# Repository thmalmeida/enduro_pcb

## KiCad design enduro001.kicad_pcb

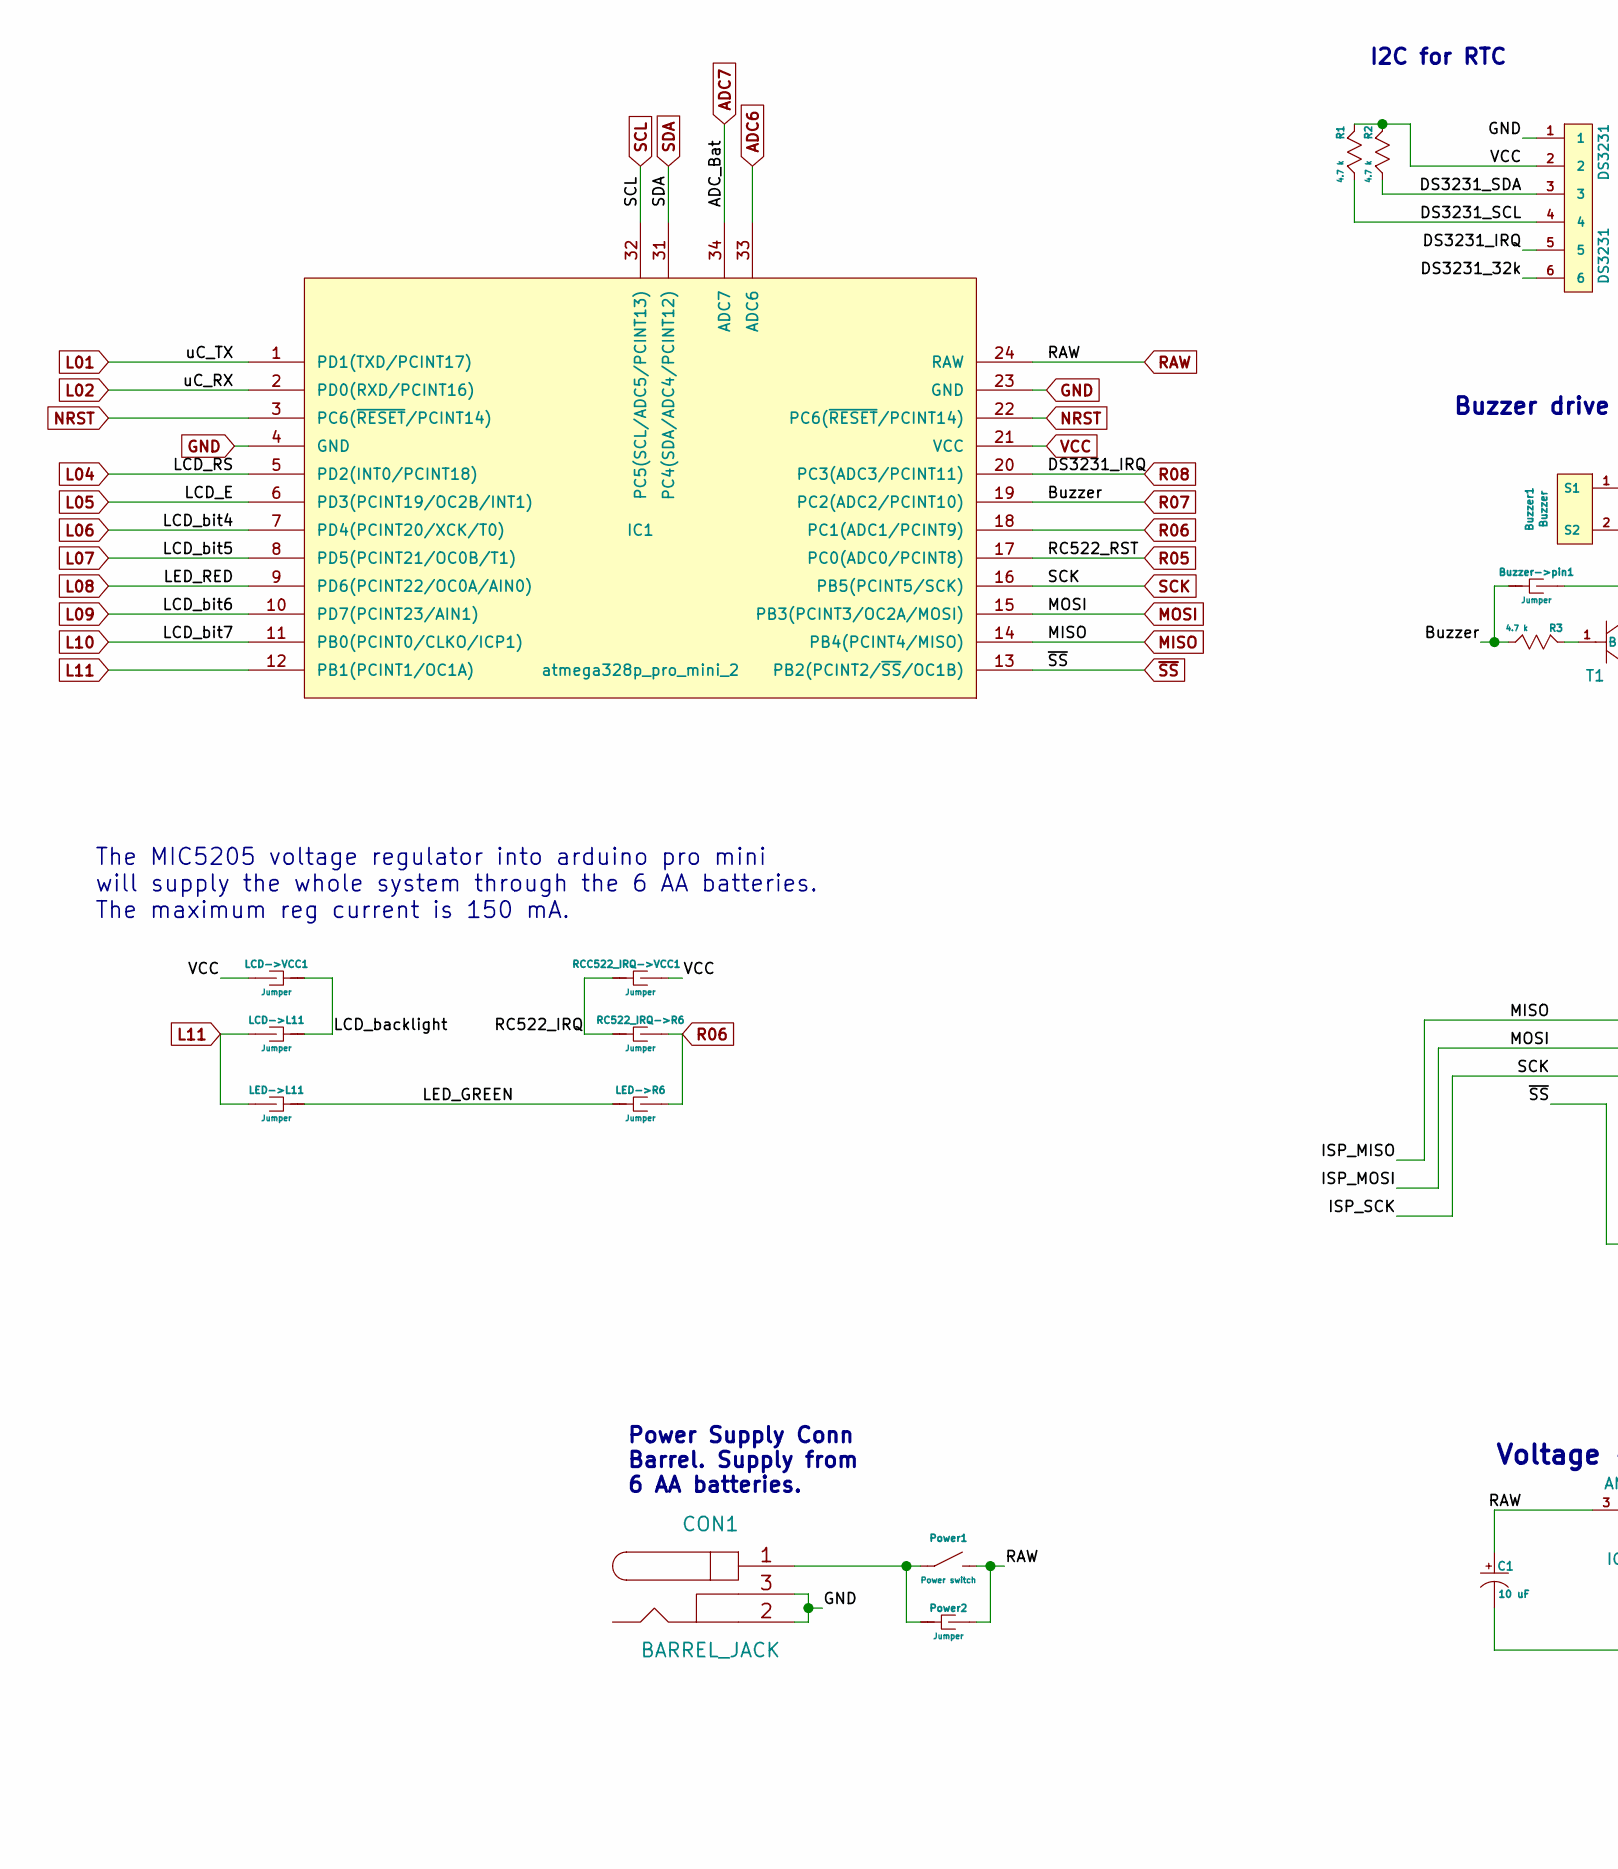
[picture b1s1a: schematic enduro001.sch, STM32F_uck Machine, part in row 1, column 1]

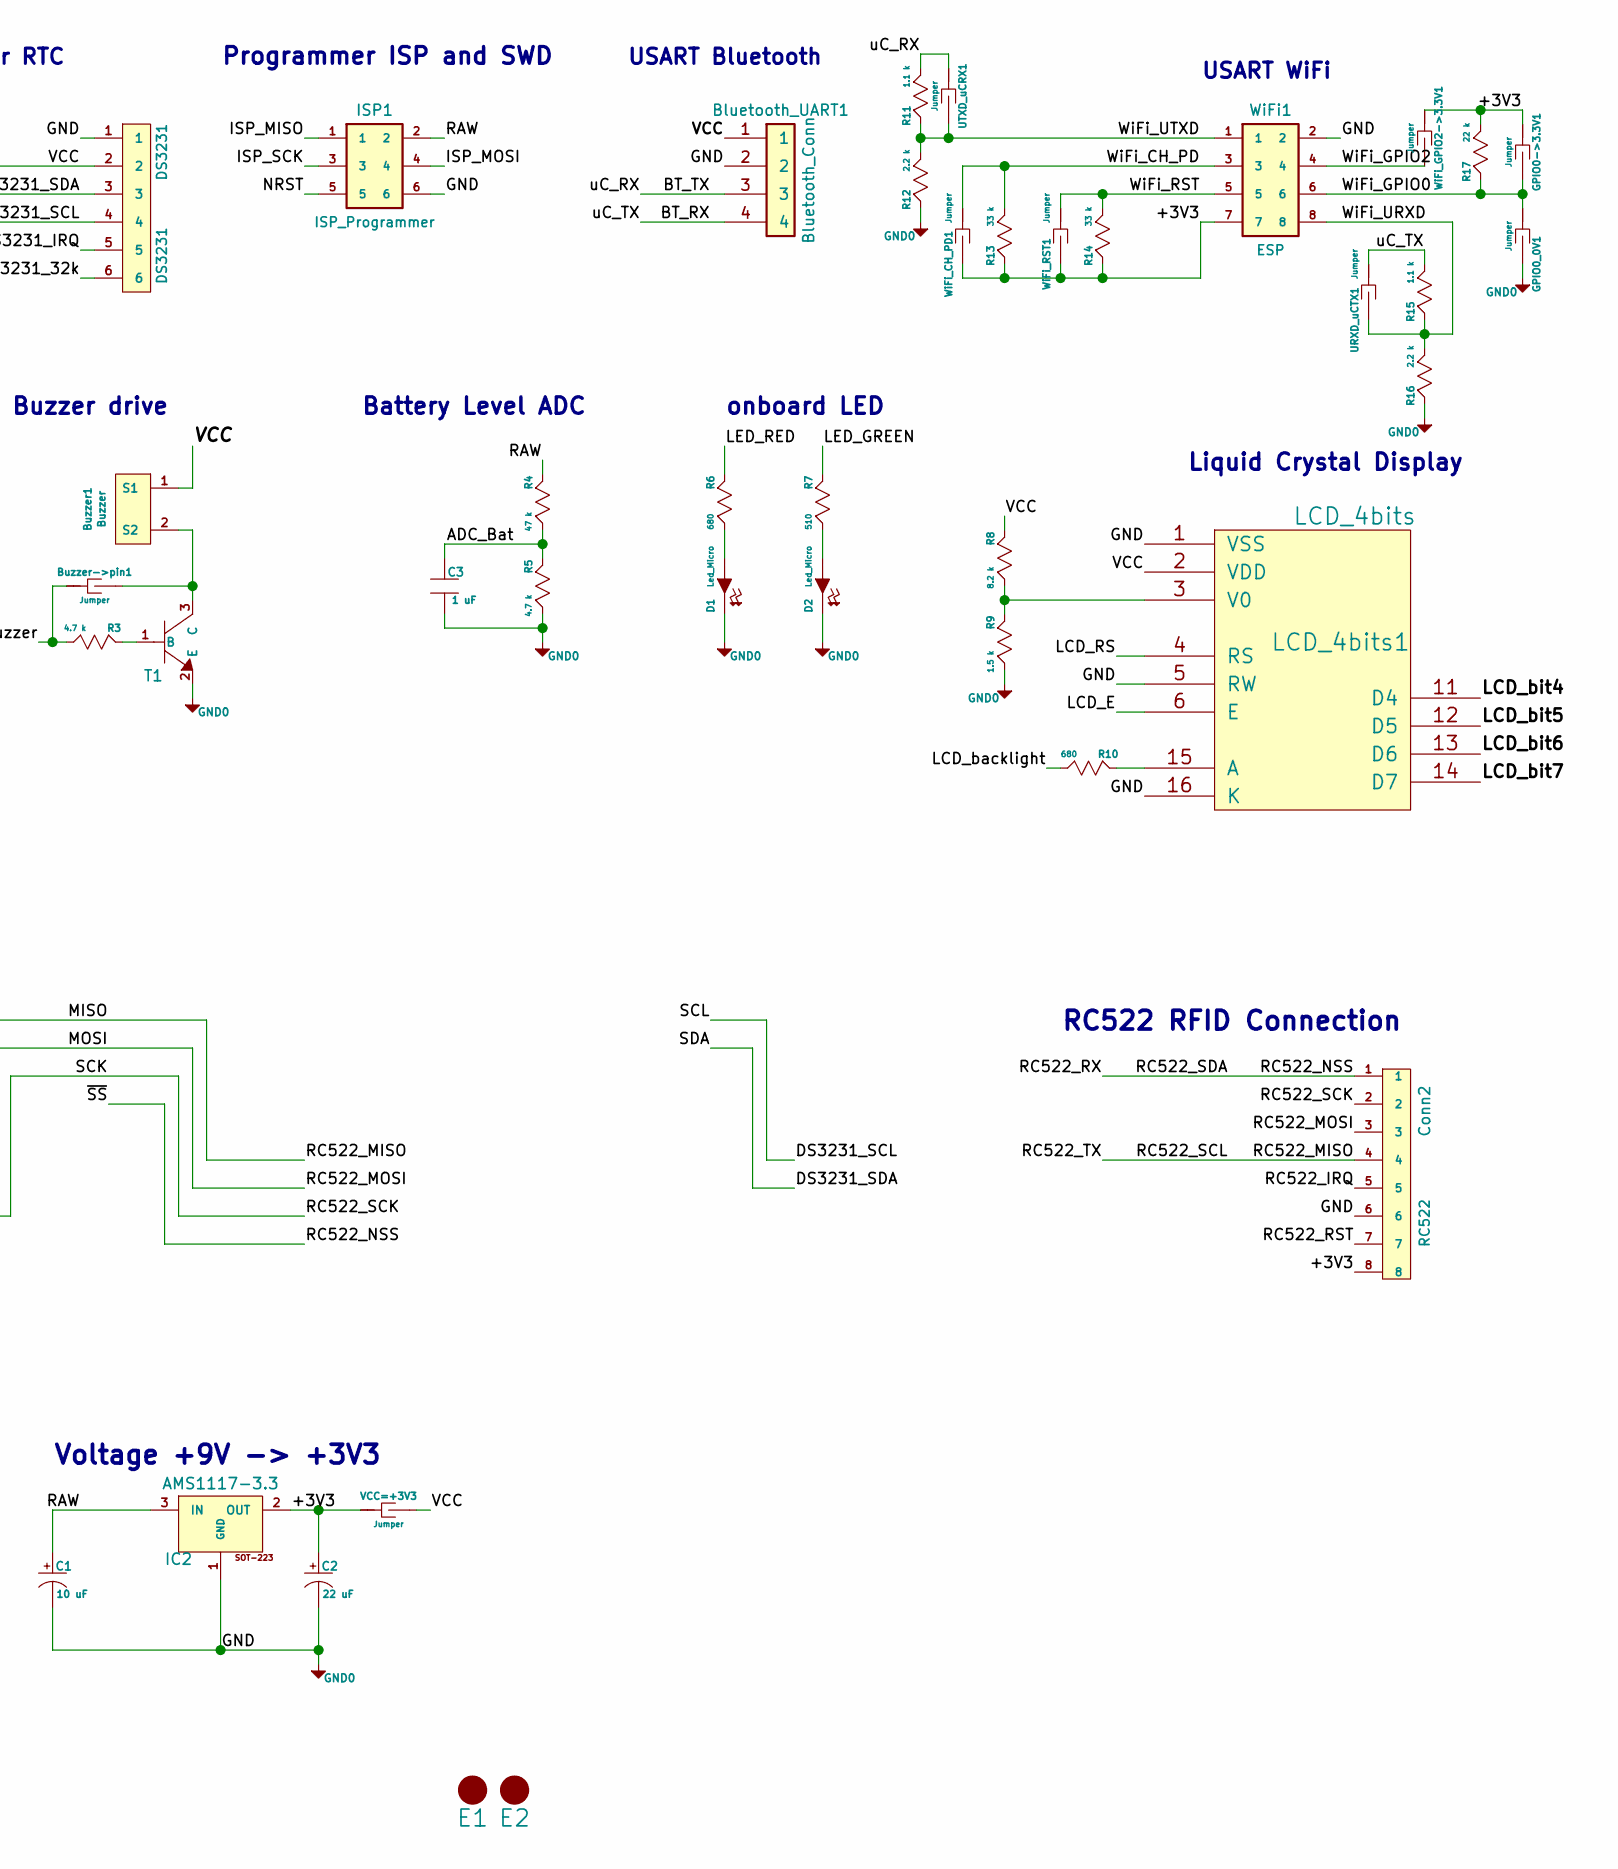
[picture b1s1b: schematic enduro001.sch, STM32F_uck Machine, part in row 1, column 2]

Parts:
Bluetooth_UART1: Bluetooth_Conn; Bluetooth_module; Part Number xxxx
Buzzer1: Buzzer; Buzzer-5V
Buzzer->pin1: Jumper; J_0603
C1: 10 uF; c_elec_5x4.5; Rated Voltage [V] vv; Tolerance [%] 10; Part Number pppp
C2: 22 uF; c_elec_5x4.5; Rated Voltage [V] vv; Tolerance [%] 10; Part Number pppp
C3: 1 uF; C_0805; Rated Voltage [V] xx; Tolerance [%] xx; Part Number xxxx
CON1: BARREL_JACK
Conn2: RC522; RC522_Module
D1, D2: Led_Micro; LED-5MM; Part Number pppp
DS3231: DS3231; DS3231_module
E1, E2: ScrewHole; ScrewHole_4.2mm
GPIO0->3.3V1, GPIO0_0V1: Jumper; J_0603
IC1: atmega328p_pro_mini_2; ARDUINO_PRO_MINI_2; Part Number atmega328p_pro_mini_2
IC2: AMS1117-3.3; SOT-223; Rated Voltage [V] 12; Part Number AMS1117-3.3
ISP1: ISP_Programmer; Pin_Header_Straight_2x03
LCD->L11: Jumper; J_0603
LCD->VCC1: Jumper; J_0603
LCD_4bits1: LCD_4bits; LCD1602A_4bits
LED->L11: Jumper; J_0603
LED->R6: Jumper; J_0603
Power1: Power switch; Pin_Header_Straight_1x02; Part Number pppp
Power2: Jumper; J_0603
R1, R2, R3, R5: 4.7 k; R_0805; Part Number MCT06030F1003C
R4: 47 k; R_0805; Part Number MCT06030F1003C
R6, R10: 680; R_0805; Part Number MCT06030F1003C
R7: 510; R_0805; Part Number MCT06030F1003C
R8: 8.2 k; R_0805; Part Number MCT06030F1003C
R9: 1.5 k; R_0805; Part Number MCT06030F1003C
R11, R15: 1.1 k; R_0805; Tolerance [%] 5; Part Number MCT08050F1001C
R12, R16: 2.2 k; R_0805; Tolerance [%] 5; Part Number MCT08050F1001C
R13, R14: 33 k; R_0805; Tolerance [%] 5; Part Number MCT08050F1001C
R17: 22 k; R_0805; Tolerance [%] 5; Part Number MCT08050F1001C
RC522_IRQ->R6: Jumper; J_0603
RCC522_IRQ->VCC1: Jumper; J_0603
T1: NPN; SOT-23; Part Number pppp
URXD_uCTX1: Jumper; J_0603
UTXD_uCRX1: Jumper; J_0603
VCC=+3V3: Jumper; J_0603
WiFi1: ESP; ESP8266_2x04_Conn
WiFi_CH_PD1: Jumper; J_0603
WiFi_GPIO2->3.3V1: Jumper; J_0603
WiFi_RST1: Jumper; J_0603

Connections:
/+3V3: C2.2, Conn2.8, GPIO0->3.3V1.1 (A), IC2.2 (OUT), R13.2 (B), R14.2 (B), R17.1 (A), VCC=+3V3.1 (A), WiFi1.7, WiFi_CH_PD1.2 (B), WiFi_GPIO2->3.3V1.1 (A), WiFi_RST1.2 (B)
/LCD_backlight: LCD->L11.1 (A), LCD->VCC1.1 (A), R10.1 (A)
/LED_GREEN: LED->L11.1 (A), LED->R6.1 (A), R7.2 (B)
/RC522_IRQ: Conn2.5, RC522_IRQ->R6.1 (A), RCC522_IRQ->VCC1.1 (A)
/WiFi_CH_PD: R13.1 (A), WiFi1.3, WiFi_CH_PD1.1 (A)
/WiFi_GPIO0: GPIO0->3.3V1.2 (B), GPIO0_0V1.1 (A), R17.2 (B), WiFi1.6
/WiFi_GPIO2: WiFi1.4, WiFi_GPIO2->3.3V1.2 (B)
/WiFi_RST: R14.1 (A), WiFi1.5, WiFi_RST1.1 (A)
/WiFi_URXD: R15.2 (B), R16.1 (A), URXD_uCTX1.2 (B), WiFi1.8
/WiFi_UTXD: R11.2 (B), R12.1 (A), UTXD_uCRX1.2 (B), WiFi1.1
ADC7: C3.1 (A), IC1.34 (ADC7), R4.1 (A), R5.2 (B)
GND: Bluetooth_UART1.2, C1.1 (GND), C2.1 (GND), C3.2 (B), CON1.2, CON1.3, Conn2.6, D1.1 (K), D2.1 (K), DS3231.1, GPIO0_0V1.2 (B), IC1.4 (GND), IC1.23 (GND), IC2.1 (GND), ISP1.6, LCD_4bits1.1 (VSS), LCD_4bits1.5 (RW), LCD_4bits1.16 (K), R5.1 (A), R9.1 (A), R12.2 (B), R16.2 (B), T1.2 (E), WiFi1.2
L01: Bluetooth_UART1.4, IC1.1 (PD1(TXD/PCINT17)), R15.1 (A), URXD_uCTX1.1 (A)
L02: Bluetooth_UART1.3, IC1.2 (PD0(RXD/PCINT16)), R11.1 (A), UTXD_uCRX1.1 (A)
L04: IC1.5 (PD2(INT0/PCINT18)), LCD_4bits1.4 (RS)
L05: IC1.6 (PD3(PCINT19/OC2B/INT1)), LCD_4bits1.6 (E)
L06: IC1.7 (PD4(PCINT20/XCK/T0)), LCD_4bits1.11 (D4)
L07: IC1.8 (PD5(PCINT21/OC0B/T1)), LCD_4bits1.12 (D5)
L08: IC1.9 (PD6(PCINT22/OC0A/AIN0)), R6.2 (B)
L09: IC1.10 (PD7(PCINT23/AIN1)), LCD_4bits1.13 (D6)
L10: IC1.11 (PB0(PCINT0/CLKO/ICP1)), LCD_4bits1.14 (D7)
L11: IC1.12 (PB1(PCINT1/OC1A)), LCD->L11.2 (B), LED->L11.2 (B)
MISO: Conn2.4, IC1.14 (PB4(PCINT4/MISO)), ISP1.1
MOSI: Conn2.3, IC1.15 (PB3(PCINT3/OC2A/MOSI)), ISP1.4
NRST: IC1.3 (PC6(~RESET~/PCINT14)), IC1.22 (PC6(~RESET~/PCINT14)), ISP1.5
unnamed: Buzzer1.2 (S2), Buzzer->pin1.2 (B), T1.3 (C)
unnamed: CON1.1, Power1.2 (B), Power2.1 (A)
unnamed: D1.2 (A), R6.1 (A)
unnamed: D2.2 (A), R7.1 (A)
unnamed: LCD_4bits1.3 (V0), R8.1 (A), R9.2 (B)
unnamed: LCD_4bits1.15 (A), R10.2 (B)
unnamed: R3.2 (B), T1.1 (B)
R05: Conn2.7, IC1.17 (PC0(ADC0/PCINT8))
R06: IC1.18 (PC1(ADC1/PCINT9)), LED->R6.2 (B), RC522_IRQ->R6.2 (B)
R07: Buzzer->pin1.1 (A), IC1.19 (PC2(ADC2/PCINT10)), R3.1 (A)
R08: DS3231.5, IC1.20 (PC3(ADC3/PCINT11))
RAW: C1.2, IC1.24 (RAW), IC2.3 (IN), ISP1.2, Power1.1 (A), Power2.2 (B), R4.2 (B)
SCK: Conn2.2, IC1.16 (PB5(PCINT5/SCK)), ISP1.3
SCL: DS3231.4, IC1.32 (PC5(SCL/ADC5/PCINT13)), R1.1 (A)
SDA: DS3231.3, IC1.31 (PC4(SDA/ADC4/PCINT12)), R2.1 (A)
VCC: Bluetooth_UART1.1, Buzzer1.1 (S1), DS3231.2, IC1.21 (VCC), LCD->VCC1.2 (B), LCD_4bits1.2 (VDD), R1.2 (B), R2.2 (B), R8.2 (B), RCC522_IRQ->VCC1.2 (B), VCC=+3V3.2 (B)
~SS: Conn2.1, IC1.13 (PB2(PCINT2/~SS~/OC1B))

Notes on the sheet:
Voltage +9V -> +3V3
USART Bluetooth
Programmer ISP and SWD
I2C for RTC
Liquid Crystal Display
onboard LED
Battery Level ADC
RC522 RFID Connection
Power Supply Conn Barrel. Supply from 6 AA batteries.
Buzzer drive
The MIC5205 voltage regulator into arduino pro mini will supply the whole system through the 6 AA batteries. The maximum reg current is 150 mA.
USART WiFi

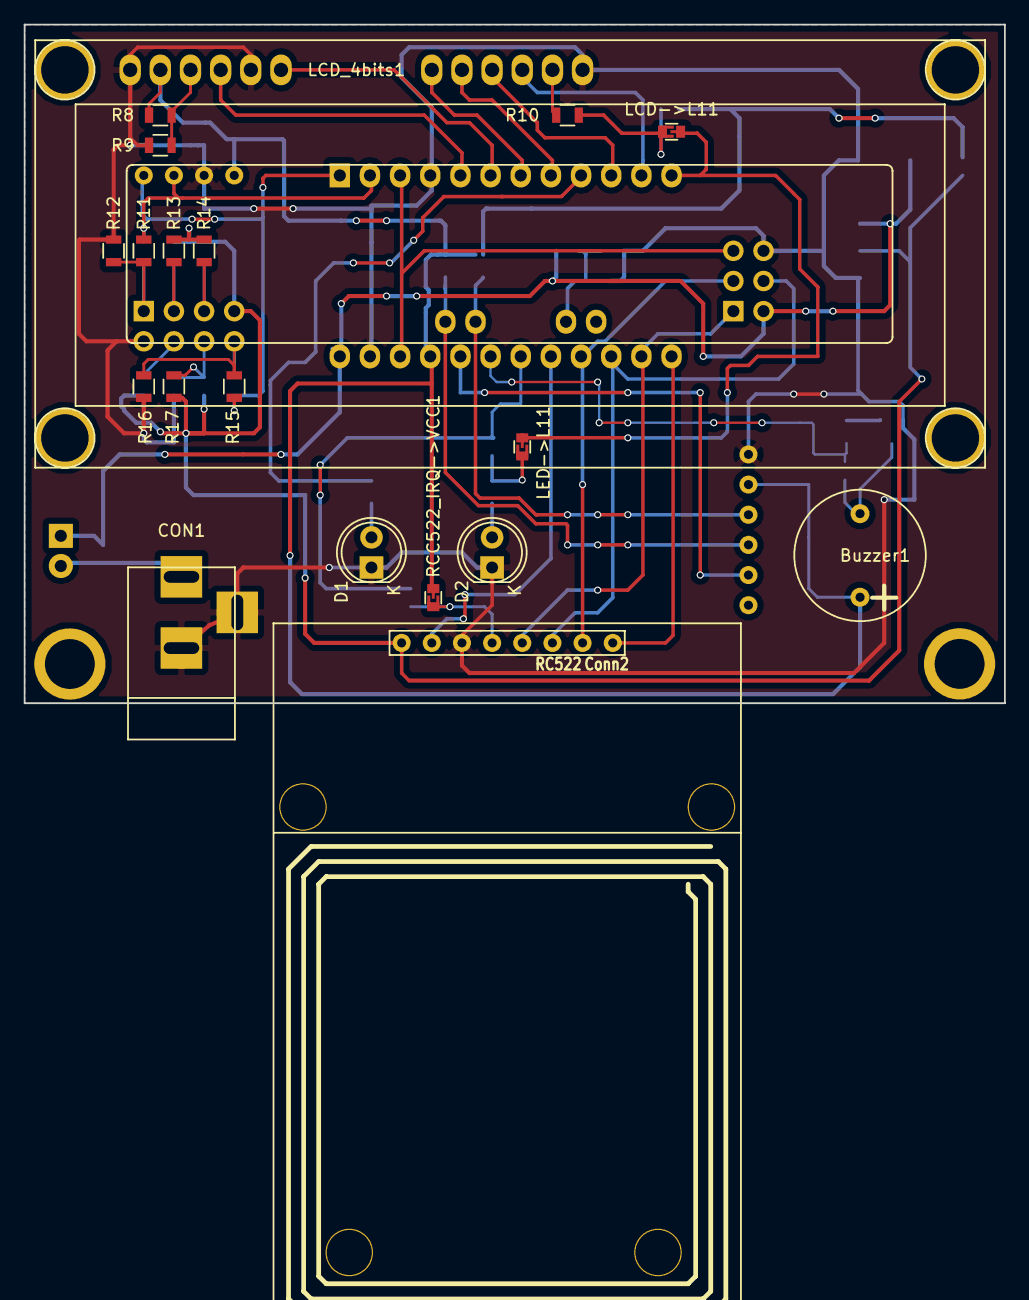
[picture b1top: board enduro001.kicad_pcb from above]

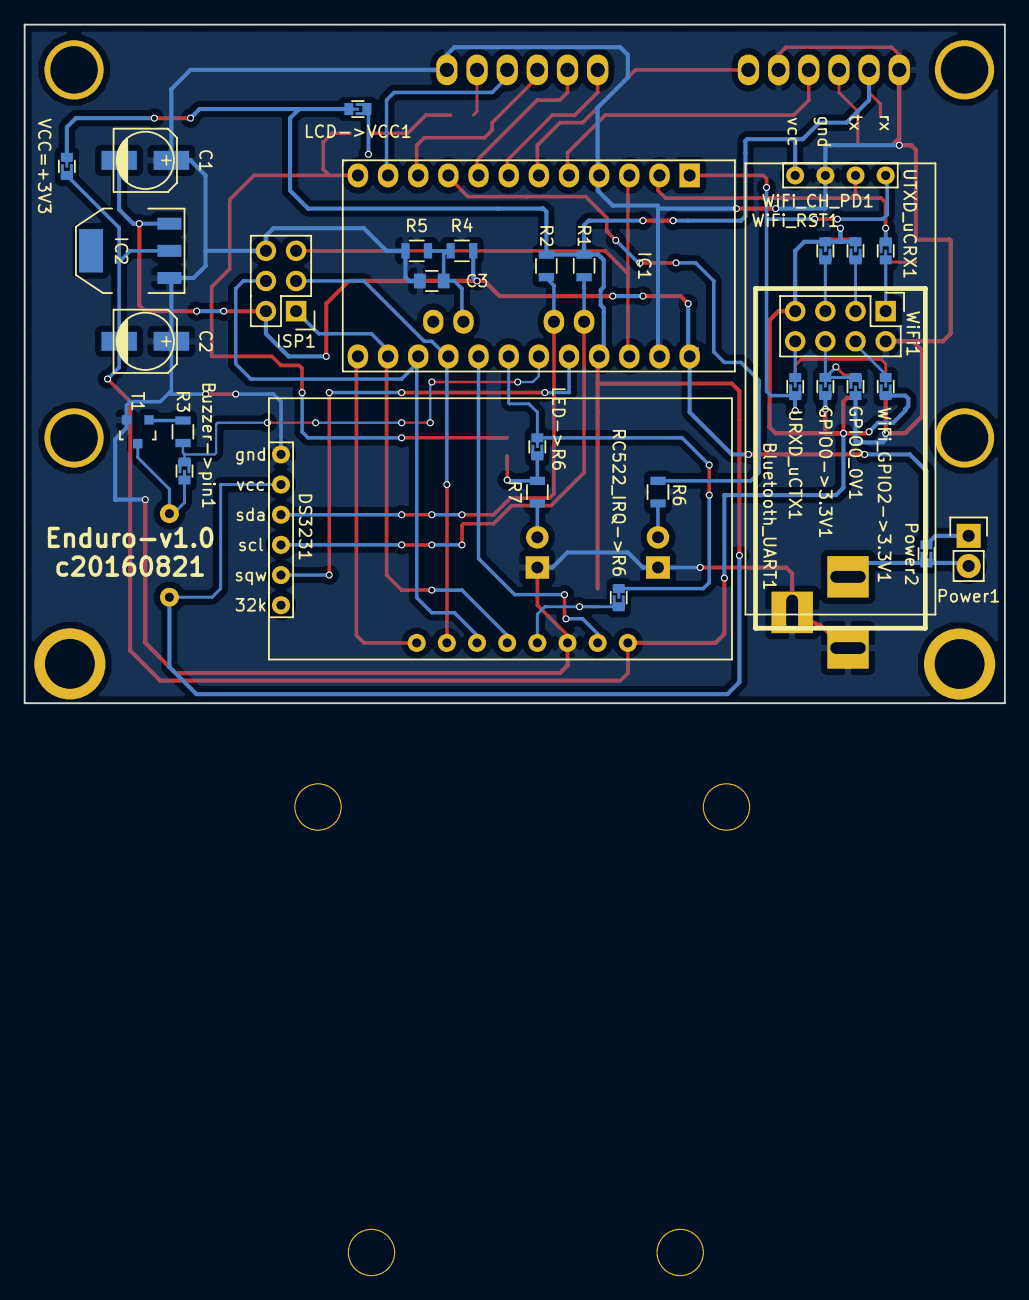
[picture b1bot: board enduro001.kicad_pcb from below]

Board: 2 copper layers, 82.5 x 57.1 mm, 52 parts (33 on the bottom side), 42 nets.

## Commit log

2016-08-29 First version manufactured
